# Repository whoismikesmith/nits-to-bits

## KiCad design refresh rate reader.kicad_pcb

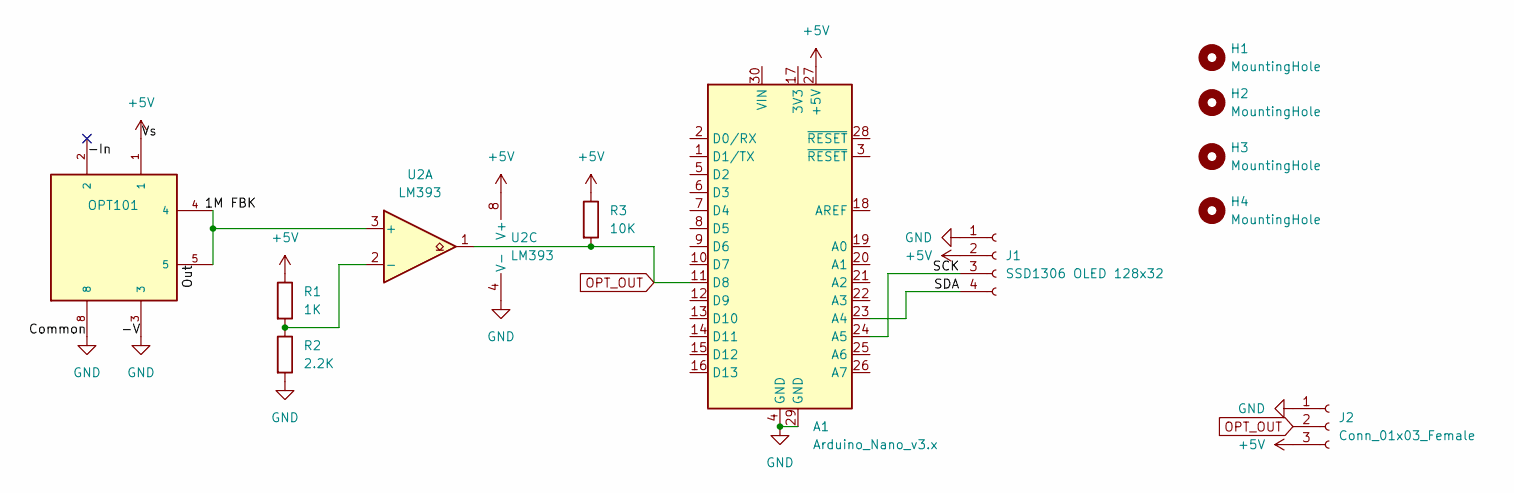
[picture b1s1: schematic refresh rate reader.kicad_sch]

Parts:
A1: Arduino_Nano_v3.x; Arduino_Nano
H1, H2, H3, H4: MountingHole; MountingHole_3.2mm_M3_ISO7380
J1: SSD1306 OLED 128x32; SSD1306-0.91-OLED-4pin-128x32
J2: Conn_01x03_Female; PinHeader_1x03_P2.54mm_Vertical
R1: 1K; R_Axial_DIN0207_L6.3mm_D2.5mm_P10.16mm_Horizontal
R2: 2.2K; R_Axial_DIN0207_L6.3mm_D2.5mm_P10.16mm_Horizontal
R3: 10K; R_Axial_DIN0207_L6.3mm_D2.5mm_P10.16mm_Horizontal
U1: OPT101; DIP-8_W7.62mm_LongPads
U2: LM393; DIP-8_W7.62mm_LongPads

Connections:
+5V: A1.27 (+5V), J1.2, J2.3, R1.1, R3.1, U1.1, U2.8 (V+)
/SCK: A1.24 (A5), J1.3
/SDA: A1.23 (A4), J1.4
GND: A1.4 (GND), A1.29 (GND), J1.1, J2.1, R2.2, U1.3, U1.8, U2.4 (V-)
unnamed: R1.2, R2.1, U2.2 (-)
unnamed: U1.4, U1.5, U2.3 (+)
OPT_OUT: A1.11 (D8), J2.2, R3.2, U2.1

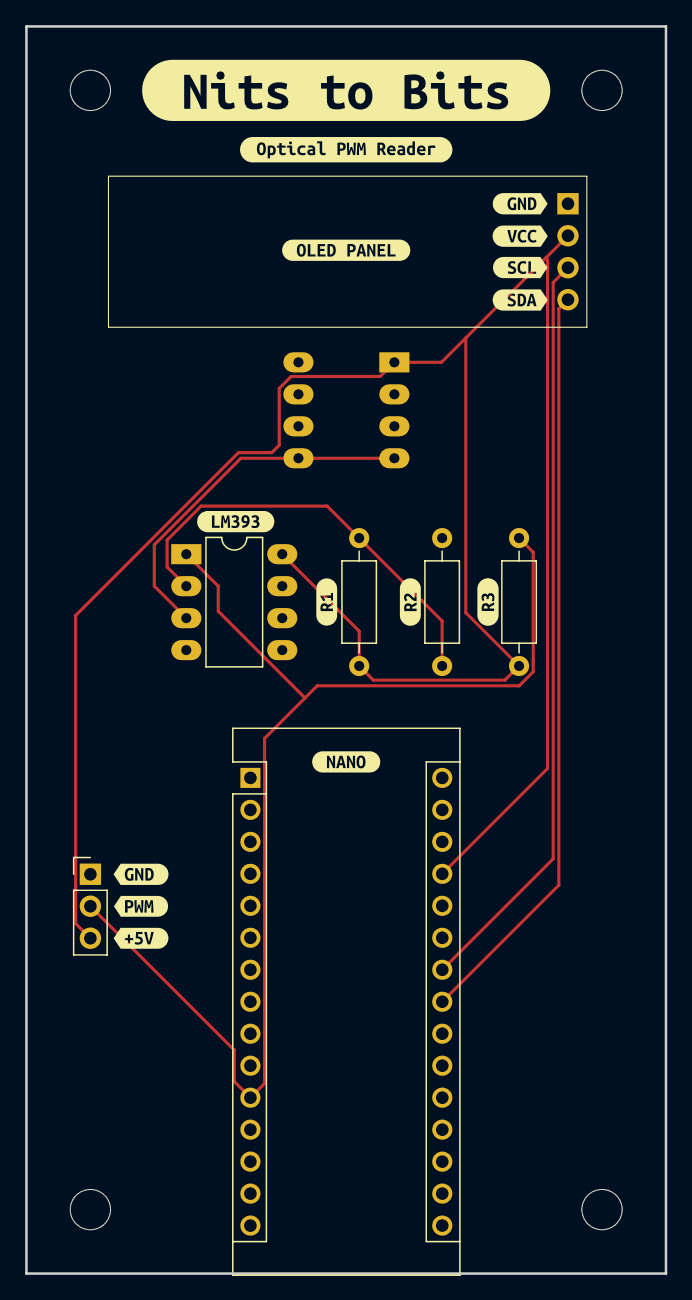
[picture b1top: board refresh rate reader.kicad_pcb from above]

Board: 2 copper layers, 50.8 x 99.1 mm, 31 parts (1 on the bottom side), 7 nets.

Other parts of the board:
kibuzzard-634C3A1E: G***; kibuzzard-634C3A1E
kibuzzard-634C3A34: G***; kibuzzard-634C3A34
kibuzzard-634C3A48: G***; kibuzzard-634C3A48
kibuzzard-634C44B9: G***; kibuzzard-634C44B9
kibuzzard-634C44DF: G***; kibuzzard-634C44DF
kibuzzard-634C45F5: G***; kibuzzard-634C45F5
kibuzzard-634C46AB: G***; kibuzzard-634C46AB
kibuzzard-634C48E5: G***; kibuzzard-634C48E5
kibuzzard-634C412A: G***; kibuzzard-634C412A
kibuzzard-634C441D: G***; kibuzzard-634C441D
kibuzzard-634C460A: G***; kibuzzard-634C460A
kibuzzard-634C461A: G***; kibuzzard-634C461A
kibuzzard-634C463E: G***; kibuzzard-634C463E
kibuzzard-634C467F: G***; kibuzzard-634C467F
kibuzzard-634C468E: G***; kibuzzard-634C468E
kibuzzard-634C469B: G***; kibuzzard-634C469B
kibuzzard-634C4154: G***; kibuzzard-634C4154
kibuzzard-634C4927: G***; kibuzzard-634C4927
kibuzzard-634C4988: G***; kibuzzard-634C4988

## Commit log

2023-09-14 add arduino sketch and pcb schematic
2023-10-31 add gerbers and kicad project
2023-10-31 stil files for 3d printed enclosure
2023-10-31 images
